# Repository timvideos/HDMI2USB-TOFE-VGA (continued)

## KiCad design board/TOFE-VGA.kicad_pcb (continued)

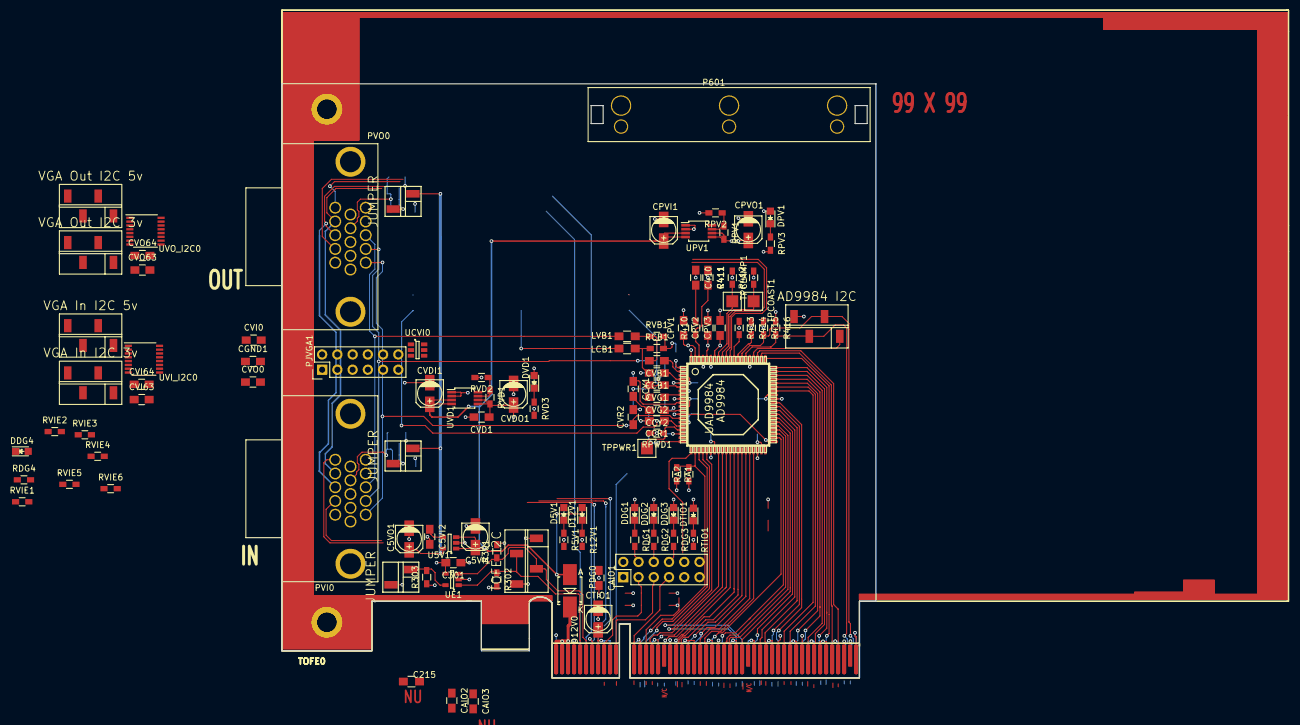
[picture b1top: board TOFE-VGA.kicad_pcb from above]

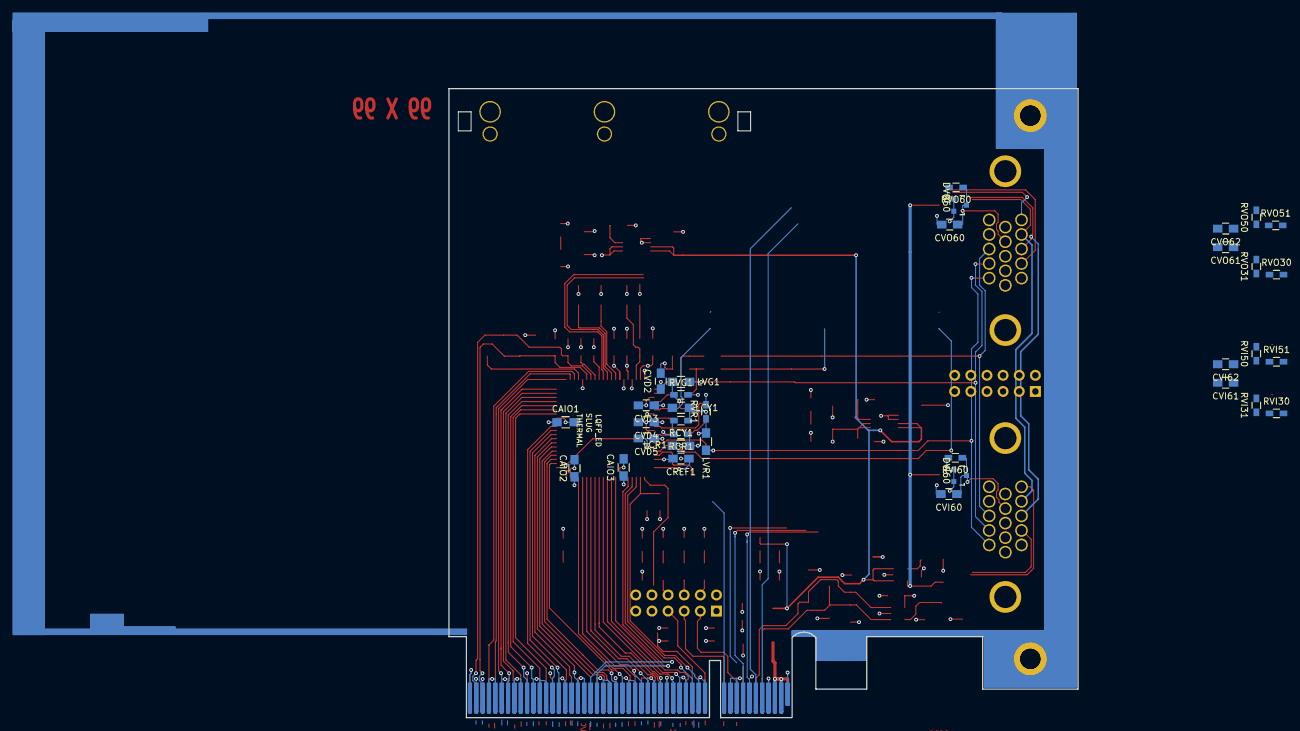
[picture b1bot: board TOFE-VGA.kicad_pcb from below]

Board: 4 copper layers, 141 parts (34 on the bottom side), 125 nets.

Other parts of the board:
C215: C5VI2; R_0805_HandSoldering
CAIO1#2, CAIO2#2, CAIO3#2: 100n; C_0805_HandSoldering
CGND1: 100n; C_0805_HandSoldering
TOFE0#2: TOFE-8X; TOFE_8X_HalfHeight

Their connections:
+3V3: CAIO1#2.1, CAIO2#2.1, CAIO3#2.1, TOFE0#2.A9, TOFE0#2.A10, TOFE0#2.B8, TOFE0#2.B10; also elsewhere on the board
/TOFE-VGA/AD9984/B0: TOFE0#2.B46; also elsewhere on the board
/TOFE-VGA/AD9984/B1: TOFE0#2.B45; also elsewhere on the board
/TOFE-VGA/AD9984/B2: TOFE0#2.A44; also elsewhere on the board
/TOFE-VGA/AD9984/B3: TOFE0#2.A43; also elsewhere on the board
/TOFE-VGA/AD9984/B4: TOFE0#2.B42; also elsewhere on the board
/TOFE-VGA/AD9984/B5: TOFE0#2.B41; also elsewhere on the board
/TOFE-VGA/AD9984/B6: TOFE0#2.A40; also elsewhere on the board
/TOFE-VGA/AD9984/B7: TOFE0#2.A39; also elsewhere on the board
/TOFE-VGA/AD9984/B8: TOFE0#2.B38; also elsewhere on the board
/TOFE-VGA/AD9984/B9: TOFE0#2.B37; also elsewhere on the board
/TOFE-VGA/AD9984/G0: TOFE0#2.A36; also elsewhere on the board
/TOFE-VGA/AD9984/G1: TOFE0#2.A35; also elsewhere on the board
/TOFE-VGA/AD9984/G2: TOFE0#2.B34; also elsewhere on the board
/TOFE-VGA/AD9984/G3: TOFE0#2.B33; also elsewhere on the board
/TOFE-VGA/AD9984/G4: TOFE0#2.A32; also elsewhere on the board
/TOFE-VGA/AD9984/G5: TOFE0#2.B30; also elsewhere on the board
/TOFE-VGA/AD9984/G6: TOFE0#2.B28; also elsewhere on the board
/TOFE-VGA/AD9984/G7: TOFE0#2.B27; also elsewhere on the board
/TOFE-VGA/AD9984/G8: TOFE0#2.A26; also elsewhere on the board
/TOFE-VGA/AD9984/G9: TOFE0#2.A25; also elsewhere on the board
/TOFE-VGA/AD9984/R0: TOFE0#2.B24; also elsewhere on the board
/TOFE-VGA/AD9984/R1: TOFE0#2.B23; also elsewhere on the board
/TOFE-VGA/AD9984/R2: TOFE0#2.A22; also elsewhere on the board
/TOFE-VGA/AD9984/R3: TOFE0#2.A21; also elsewhere on the board
/TOFE-VGA/AD9984/R4: TOFE0#2.B20; also elsewhere on the board
/TOFE-VGA/AD9984/R5: TOFE0#2.B19; also elsewhere on the board
/TOFE-VGA/AD9984/R6: TOFE0#2.A19; also elsewhere on the board
/TOFE-VGA/AD9984/R7: TOFE0#2.A17; also elsewhere on the board
/TOFE-VGA/AD9984/R8: TOFE0#2.A16; also elsewhere on the board
/TOFE-VGA/AD9984/R9: TOFE0#2.B15; also elsewhere on the board
/TOFE-VGA/TOFE/IDCLK: TOFE0#2.B5; also elsewhere on the board
/TOFE-VGA/TOFE/IDDAT: TOFE0#2.B6; also elsewhere on the board
/TOFE-VGA/TOFE/RAW_VCC12V: TOFE0#2.A2, TOFE0#2.A3, TOFE0#2.B1, TOFE0#2.B2, TOFE0#2.B3; also elsewhere on the board
GND: C215.2, CAIO1#2.2, CAIO2#2.2, CAIO3#2.2, CGND1.1, TOFE0#2.A4, TOFE0#2.A12, TOFE0#2.A15, TOFE0#2.A18, TOFE0#2.A20, TOFE0#2.A23, TOFE0#2.A24, TOFE0#2.A27, TOFE0#2.A28, TOFE0#2.A31, TOFE0#2.A34, TOFE0#2.A37, TOFE0#2.A38, TOFE0#2.A41, TOFE0#2.A42, TOFE0#2.A45, TOFE0#2.A46, TOFE0#2.A49, TOFE0#2.B4, TOFE0#2.B7, TOFE0#2.B13, TOFE0#2.B16, TOFE0#2.B18, TOFE0#2.B21, TOFE0#2.B22, TOFE0#2.B25, TOFE0#2.B26, TOFE0#2.B29, TOFE0#2.B32, TOFE0#2.B35, TOFE0#2.B36, TOFE0#2.B39, TOFE0#2.B40, TOFE0#2.B43, TOFE0#2.B44, TOFE0#2.B47, TOFE0#2.B49; also elsewhere on the board
GNDA: CGND1.2; also elsewhere on the board
unnamed 124: TOFE0#2.B12; also elsewhere on the board
unnamed 139: TOFE0#2.A33; also elsewhere on the board
unnamed 140: TOFE0#2.B17; also elsewhere on the board
unnamed 141: TOFE0#2.B31; also elsewhere on the board
PRNST: TOFE0#2.A1, TOFE0#2.B48; also elsewhere on the board

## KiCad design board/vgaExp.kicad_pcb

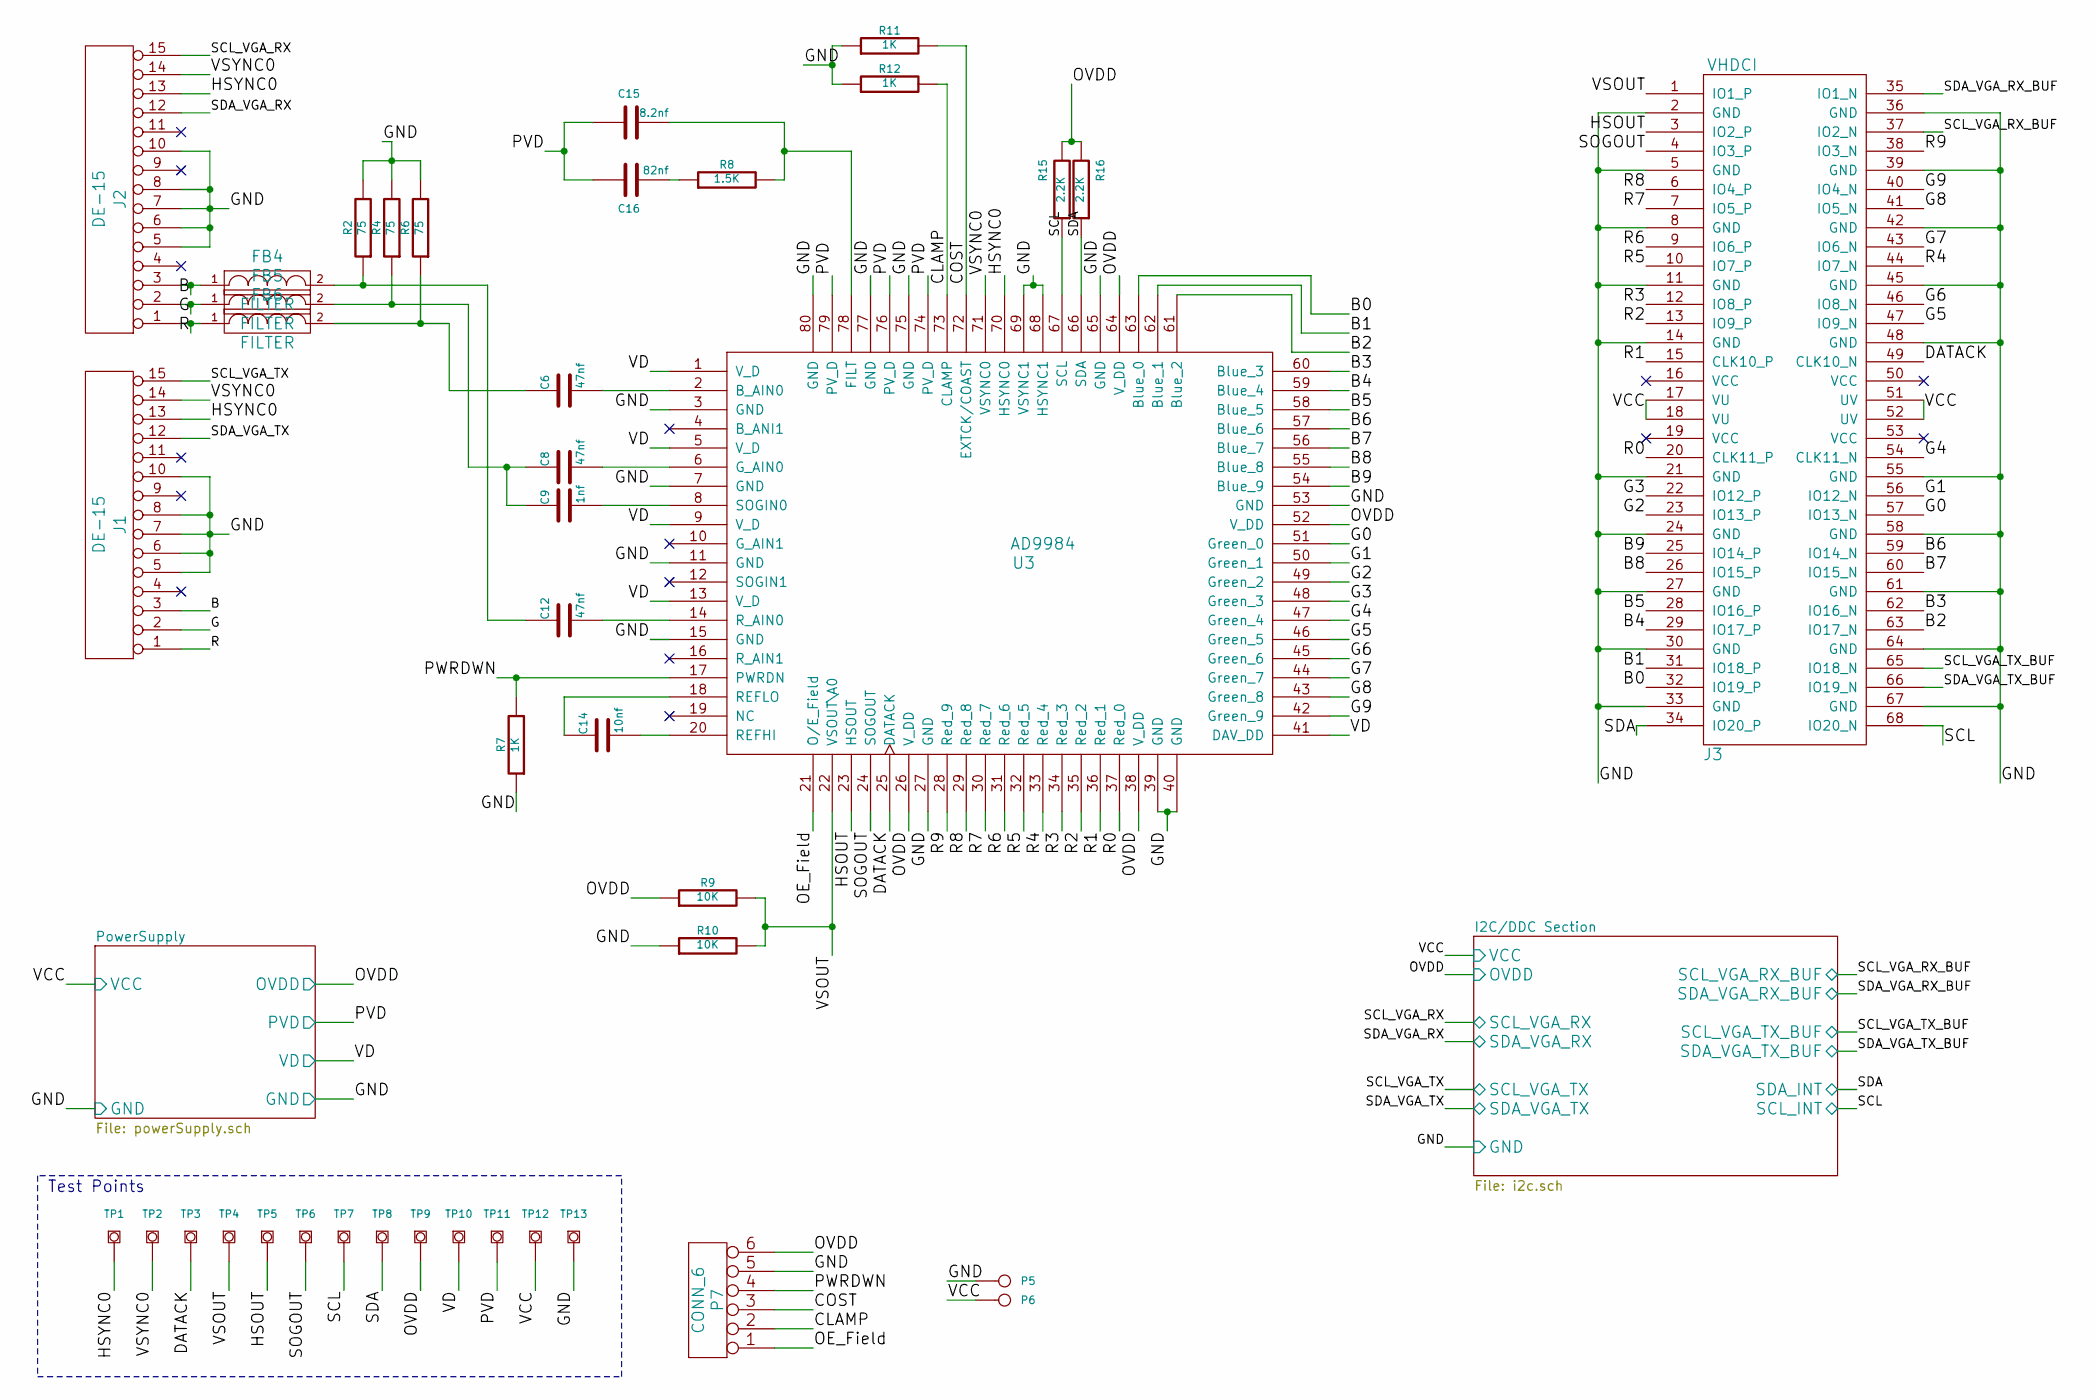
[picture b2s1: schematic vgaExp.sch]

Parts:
C6, C8, C12: 47nf
C9: 1nf
C14: 10nf
C15: 8.2nf
C16: 82nf
FB4, FB5, FB6: FILTER
J1, J2: DE-15
J3: VHDCI
P5, P6: CONN_1
P7: CONN_6
R2, R4, R6: 75
R7, R11, R12: 1K
R8: 1.5K
R9, R10: 10K
R15, R16: 2.2K
TP1, TP2, TP3, TP4, TP5, TP6, TP7, TP8, TP9, TP10, TP11, TP12, TP13: TESTPOINT
U3: AD9984

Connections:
/B: FB4.1, J1.3, J2.3
/B0: J3.32 (IO19_P), U3.63 (Blue_0)
/B1: J3.31 (IO18_P), U3.62 (Blue_1)
/B2: J3.63 (IO17_N), U3.61 (Blue_2)
/B3: J3.62 (IO16_N), U3.60 (Blue_3)
/B4: J3.29 (IO17_P), U3.59 (Blue_4)
/B5: J3.28 (IO16_P), U3.58 (Blue_5)
/B6: J3.59 (IO14_N), U3.57 (Blue_6)
/B7: J3.60 (IO15_N), U3.56 (Blue_7)
/B8: J3.26 (IO15_P), U3.55 (Blue_8)
/B9: J3.25 (IO14_P), U3.54 (Blue_9)
/CLAMP: P7.2, R12.2, U3.73 (CLAMP)
/COST: P7.3, R11.2, U3.72 (EXTCK/COAST)
/DATACK: J3.49 (CLK10_N), TP3.1, U3.25 (DATACK)
/G: FB5.1, J1.2, J2.2
/G0: J3.57 (IO13_N), U3.51 (Green_0)
/G1: J3.56 (IO12_N), U3.50 (Green_1)
/G2: J3.23 (IO13_P), U3.49 (Green_2)
/G3: J3.22 (IO12_P), U3.48 (Green_3)
/G4: J3.54 (CLK11_N), U3.47 (Green_4)
/G5: J3.47 (IO9_N), U3.46 (Green_5)
/G6: J3.46 (IO8_N), U3.45 (Green_6)
/G7: J3.43 (IO6_N), U3.44 (Green_7)
/G8: J3.41 (IO5_N), U3.43 (Green_8)
/G9: J3.40 (IO4_N), U3.42 (Green_9)
/HSOUT: J3.3 (IO2_P), TP5.1, U3.23 (HSOUT)
/HSYNC0: J1.13, J2.13, TP1.1, U3.70 (HSYNC0)
/I2C/DDC Section/SCL_INT: J3.68 (IO20_N), R15.1, TP7.1, U3.67 (SCL); also elsewhere on the board
/I2C/DDC Section/SCL_VGA_RX: J2.15; also elsewhere on the board
/I2C/DDC Section/SCL_VGA_RX_BUF: J3.37 (IO2_N); also elsewhere on the board
/I2C/DDC Section/SCL_VGA_TX: J1.15; also elsewhere on the board
/I2C/DDC Section/SCL_VGA_TX_BUF: J3.65 (IO18_N); also elsewhere on the board
/I2C/DDC Section/SDA_INT: J3.34 (IO20_P), R16.1, TP8.1, U3.66 (SDA); also elsewhere on the board
/I2C/DDC Section/SDA_VGA_RX: J2.12; also elsewhere on the board
/I2C/DDC Section/SDA_VGA_RX_BUF: J3.35 (IO1_N); also elsewhere on the board
/I2C/DDC Section/SDA_VGA_TX: J1.12; also elsewhere on the board
/I2C/DDC Section/SDA_VGA_TX_BUF: J3.66 (IO19_N); also elsewhere on the board
/I2C/DDC Section/VCC: J3.17 (VU), J3.18 (VU), J3.51 (UV), J3.52 (UV), P6.1, TP12.1; also elsewhere on the board
/OE_Field: P7.1, U3.21 (O/E_Field)
/PWRDWN: P7.4, R7.2, U3.17 (PWRDN)
/PowerSupply/PVD: C15.1, C16.1, TP11.1, U3.74 (PV_D), U3.76 (PV_D), U3.79 (PV_D); also elsewhere on the board
/PowerSupply/VD: TP10.1, U3.1 (V_D), U3.5 (V_D), U3.9 (V_D), U3.13 (V_D), U3.41 (DAV_DD); also elsewhere on the board
/R: FB6.1, J1.1, J2.1
/R0: J3.20 (CLK11_P), U3.37 (Red_0)
/R1: J3.15 (CLK10_P), U3.36 (Red_1)
/R2: J3.13 (IO9_P), U3.35 (Red_2)
/R3: J3.12 (IO8_P), U3.34 (Red_3)
/R4: J3.44 (IO7_N), U3.33 (Red_4)
/R5: J3.10 (IO7_P), U3.32 (Red_5)
/R6: J3.9 (IO6_P), U3.31 (Red_6)
/R7: J3.7 (IO5_P), U3.30 (Red_7)
/R8: J3.6 (IO4_P), U3.29 (Red_8)
/R9: J3.38 (IO3_N), U3.28 (Red_9)
/SOGOUT: J3.4 (IO3_P), TP6.1, U3.24 (SOGOUT)
/VSOUT: J3.1 (IO1_P), R9.2, R10.2, TP4.1, U3.22 (VSOUT\A0)
/VSYNC0: J1.14, J2.14, TP2.1, U3.71 (VSYNC0)
unnamed: C15.2, R8.2, U3.78 (FILT)
unnamed: C16.2, R8.1
unnamed: C6.2, U3.2 (B_AIN0)
unnamed: C8.2, U3.6 (G_AIN0)
unnamed: C9.2, U3.8 (SOGIN0)
unnamed: C12.2, U3.14 (R_AIN0)
unnamed: C12.1, FB4.2, R2.1
unnamed: C8.1, C9.1, FB5.2, R4.1
unnamed: C6.1, FB6.2, R6.1
unnamed: C14.2, U3.20 (REFHI)
unnamed: C14.1, U3.18 (REFLO)

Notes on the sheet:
Test Points

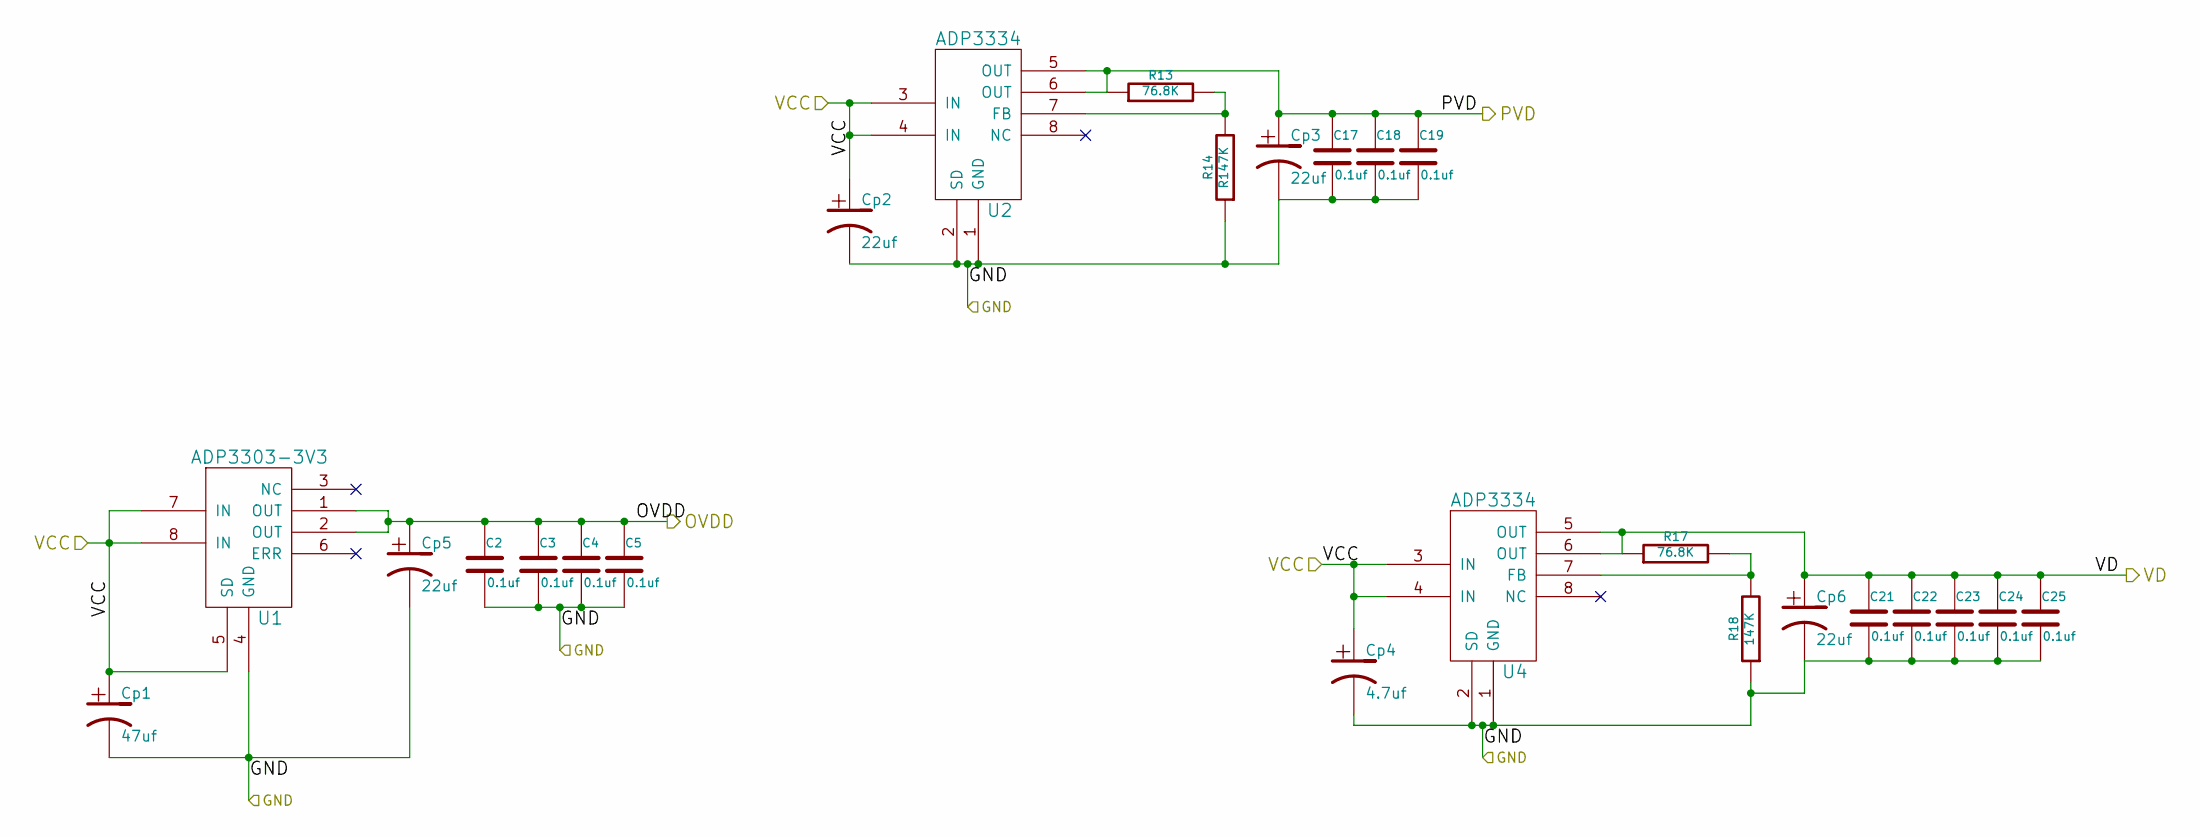
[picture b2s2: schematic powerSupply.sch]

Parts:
C2, C3, C4, C5, C17, C18, C19, C21, C22, C23, C24, C25: 0.1uf
Cp1: 47uf
Cp2, Cp3, Cp5, Cp6: 22uf
Cp4: 4.7uf
R13, R17: 76.8K
R14: R147K
R18: 147K
U1: ADP3303-3V3
U2, U4: ADP3334

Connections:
/I2C/DDC Section/VCC: Cp1.1, Cp2.1, Cp4.1, U1.5 (SD), U1.7 (IN), U1.8 (IN), U2.3 (IN), U2.4 (IN), U4.3 (IN), U4.4 (IN); also elsewhere on the board
/PowerSupply/PVD: C17.1, C18.1, C19.1, Cp3.1, R13.1, U2.5 (OUT), U2.6 (OUT); also elsewhere on the board
/PowerSupply/VD: C21.1, C22.1, C23.1, C24.1, C25.1, Cp6.1, R17.1, U4.5 (OUT), U4.6 (OUT); also elsewhere on the board
unnamed: R13.2, R14.2, U2.7 (FB)
unnamed: R17.2, R18.2, U4.7 (FB)

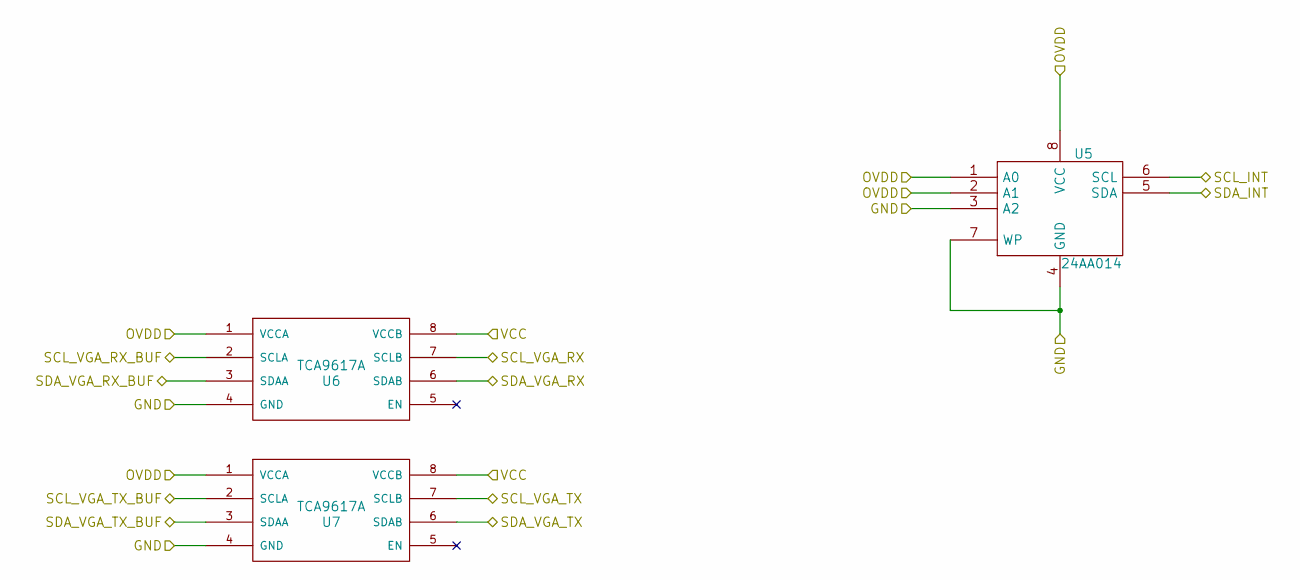
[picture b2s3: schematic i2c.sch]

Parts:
U5: 24AA014
U6, U7: TCA9617A

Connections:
/I2C/DDC Section/SCL_INT: U5.6 (SCL); also elsewhere on the board
/I2C/DDC Section/SCL_VGA_RX: U6.7 (SCLB); also elsewhere on the board
/I2C/DDC Section/SCL_VGA_RX_BUF: U6.2 (SCLA); also elsewhere on the board
/I2C/DDC Section/SCL_VGA_TX: U7.7 (SCLB); also elsewhere on the board
/I2C/DDC Section/SCL_VGA_TX_BUF: U7.2 (SCLA); also elsewhere on the board
/I2C/DDC Section/SDA_INT: U5.5 (SDA); also elsewhere on the board
/I2C/DDC Section/SDA_VGA_RX: U6.6 (SDAB); also elsewhere on the board
/I2C/DDC Section/SDA_VGA_RX_BUF: U6.3 (SDAA); also elsewhere on the board
/I2C/DDC Section/SDA_VGA_TX: U7.6 (SDAB); also elsewhere on the board
/I2C/DDC Section/SDA_VGA_TX_BUF: U7.3 (SDAA); also elsewhere on the board
/I2C/DDC Section/VCC: U6.8 (VCCB), U7.8 (VCCB); also elsewhere on the board

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
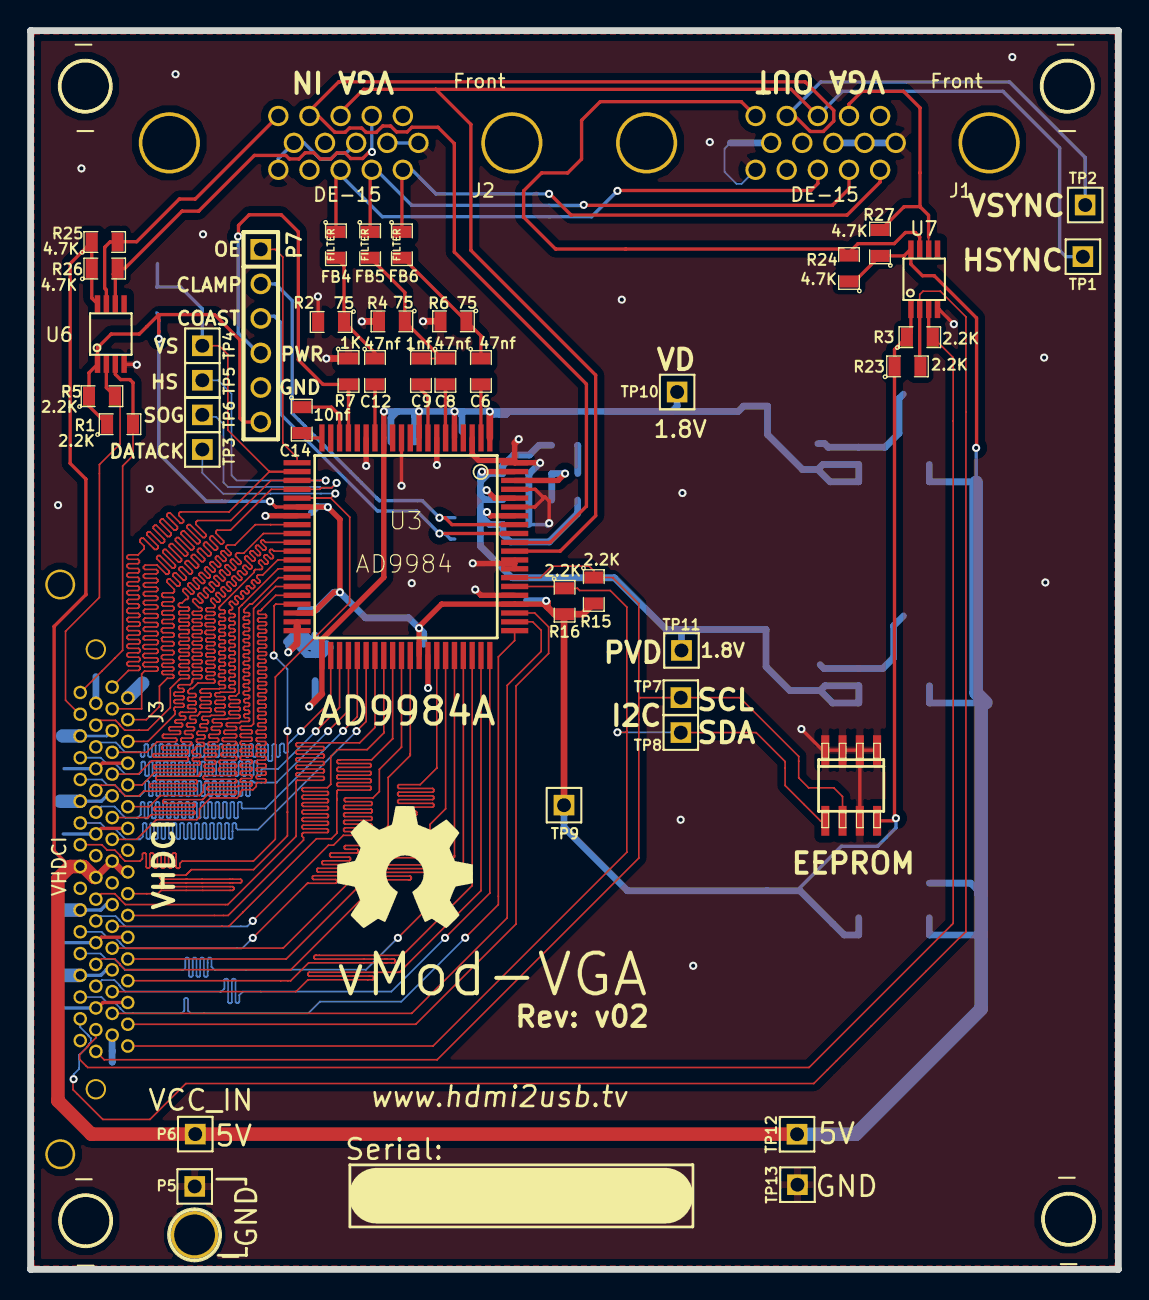
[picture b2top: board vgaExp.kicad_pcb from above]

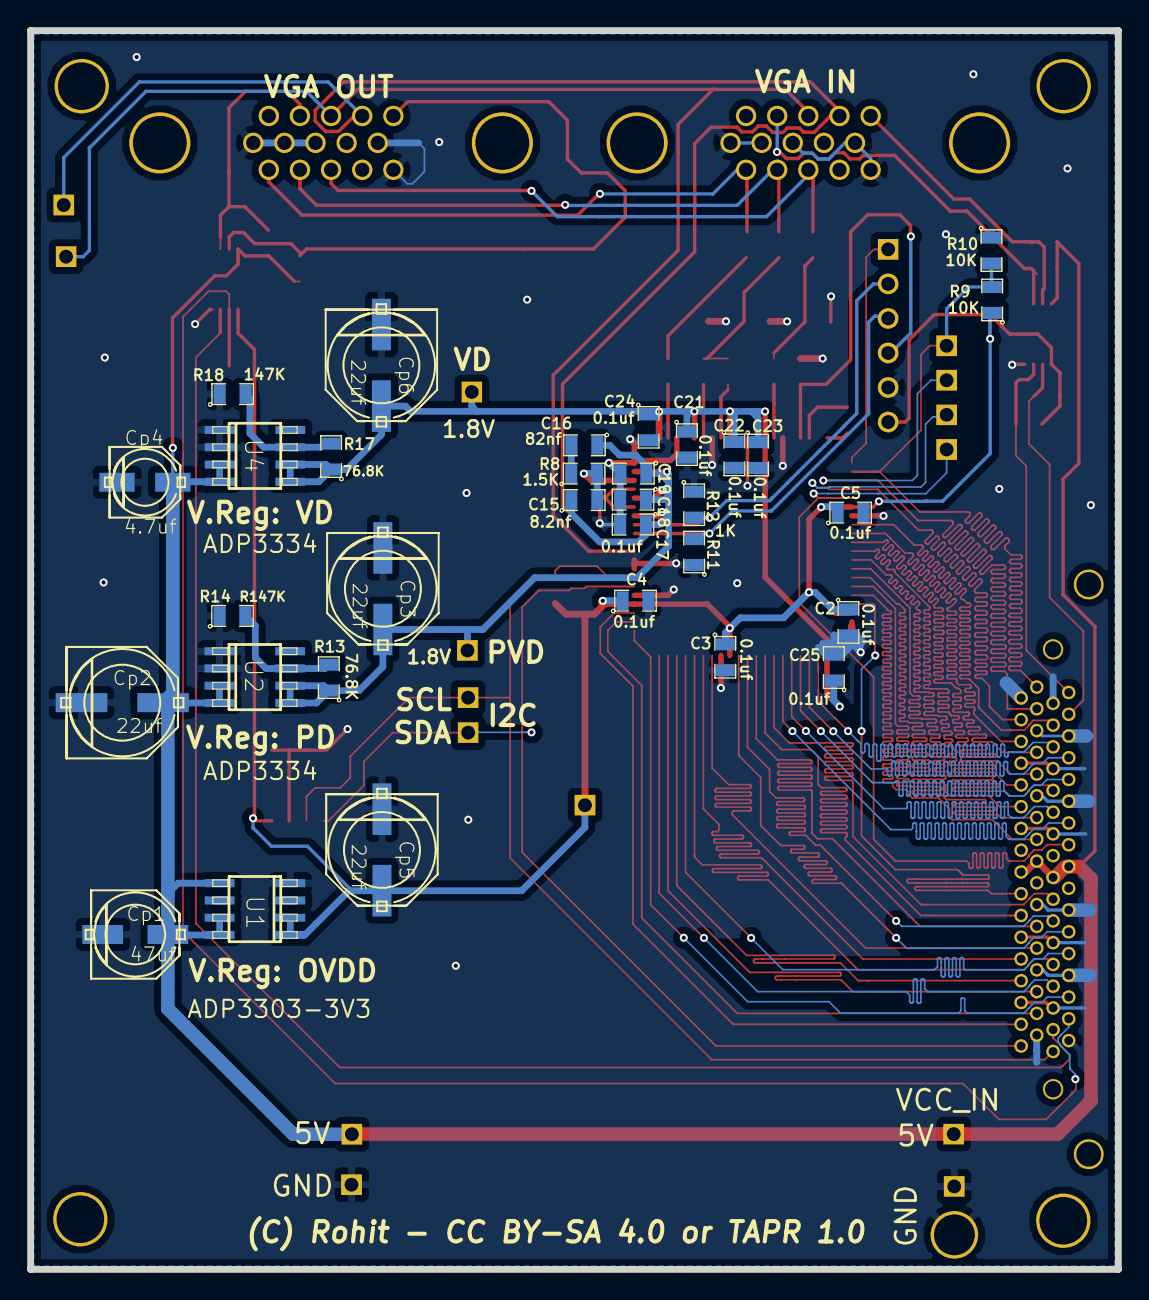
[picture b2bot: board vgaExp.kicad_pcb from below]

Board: 2 copper layers, 80.0 x 91.1 mm, 83 parts (32 on the bottom side), 71 nets.

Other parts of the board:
-: -; STAND-OFF
-#2, -#3, -#4: -; STAND-OFF
-#5: GND-HOLE
R1, R3, R5, R23: 2.2K; SM0805
R24, R25, R26, R27: 4.7K; SM0805
l1: e; OSHW-logo_silkscreen-back_10mm

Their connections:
/I2C/DDC Section/SCL_VGA_RX: R25.2; also elsewhere on the board
/I2C/DDC Section/SCL_VGA_RX_BUF: R5.2; also elsewhere on the board
/I2C/DDC Section/SCL_VGA_TX: R24.2; also elsewhere on the board
/I2C/DDC Section/SCL_VGA_TX_BUF: R23.2; also elsewhere on the board
/I2C/DDC Section/SDA_VGA_RX: R26.2; also elsewhere on the board
/I2C/DDC Section/SDA_VGA_RX_BUF: R1.2; also elsewhere on the board
/I2C/DDC Section/SDA_VGA_TX: R27.2; also elsewhere on the board
/I2C/DDC Section/SDA_VGA_TX_BUF: R3.2; also elsewhere on the board
/I2C/DDC Section/VCC: R24.1, R25.1, R26.1, R27.1; also elsewhere on the board

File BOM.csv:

1nf,2,"C9 C11"
8.2nf,1,"C15"
47nf,6,"C6 C7 C8 C10 C12 C13"
82nf,1,"C16"
10uf,1,"C14"
.1uf,12,"C2 C3 C4 C5 C17 C18 C19 C21 C22 C23 C24 C25"
4.7uf,1,"Cp4"
22uf,4,"Cp2 Cp3 Cp5 Cp6"
47uf,1,"Cp1"
FILTER,6,"FB1 FB2 FB3 FB4 FB5 FB6"
DE-15,2,"J1 J2"
VHDCI,1,"J3"
75,6,"R1 R2 R3 R4 R5 R6"
1K,3,"R7 R11 R12"
1.5K,1,"R8"
2.2K,2,"R15 R16"
10K,2,"R9 R10"
76.8k,2,"R13 R17"
147k,2,"R14 R18"
ADP3303-3V3,1,"U1"
ADP3334,2,"U2 U4"
AD9984,1,"U3"

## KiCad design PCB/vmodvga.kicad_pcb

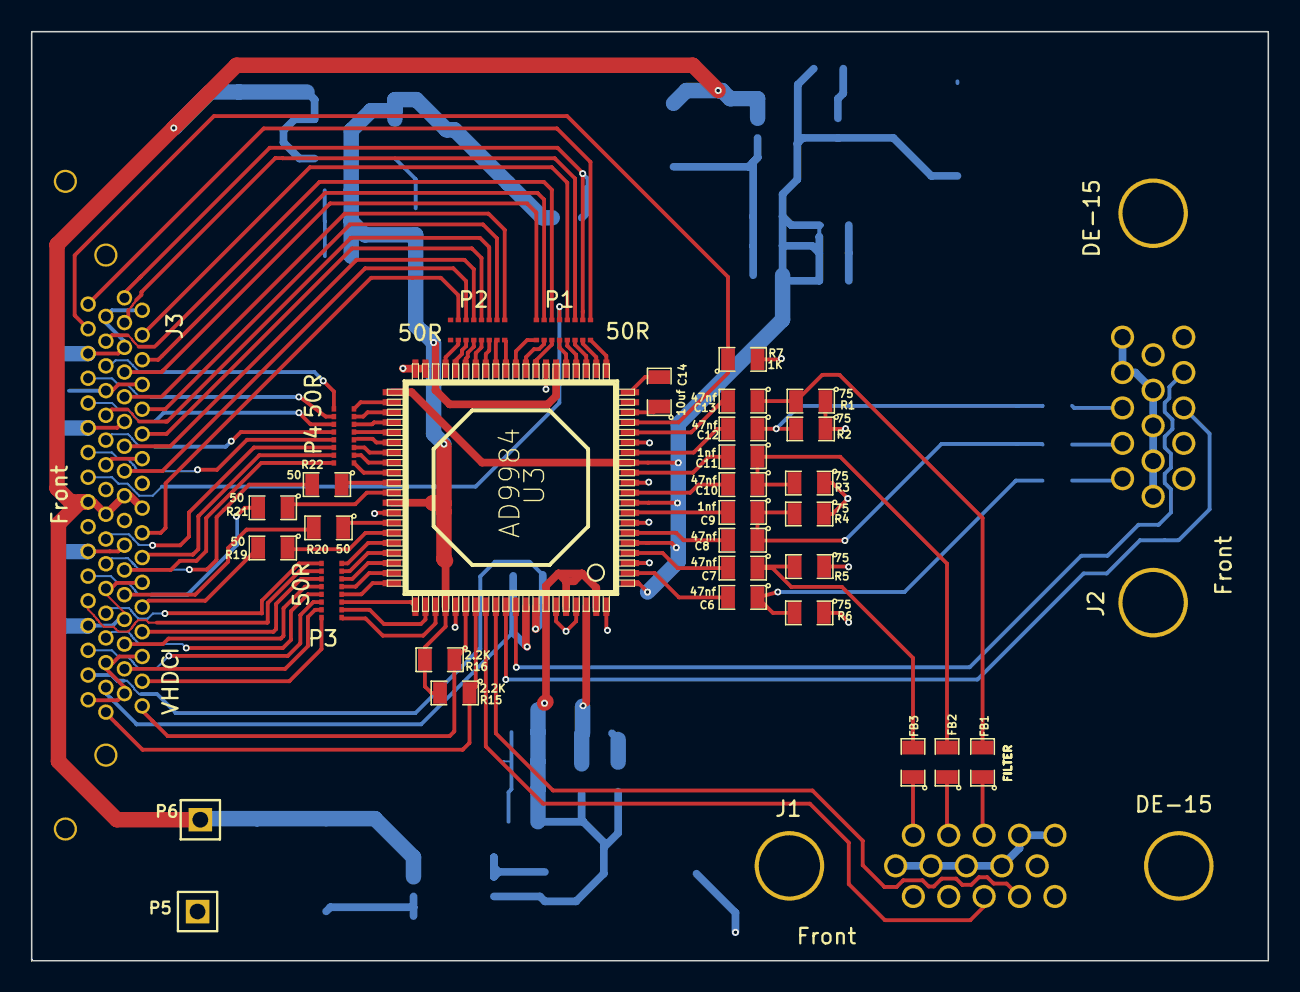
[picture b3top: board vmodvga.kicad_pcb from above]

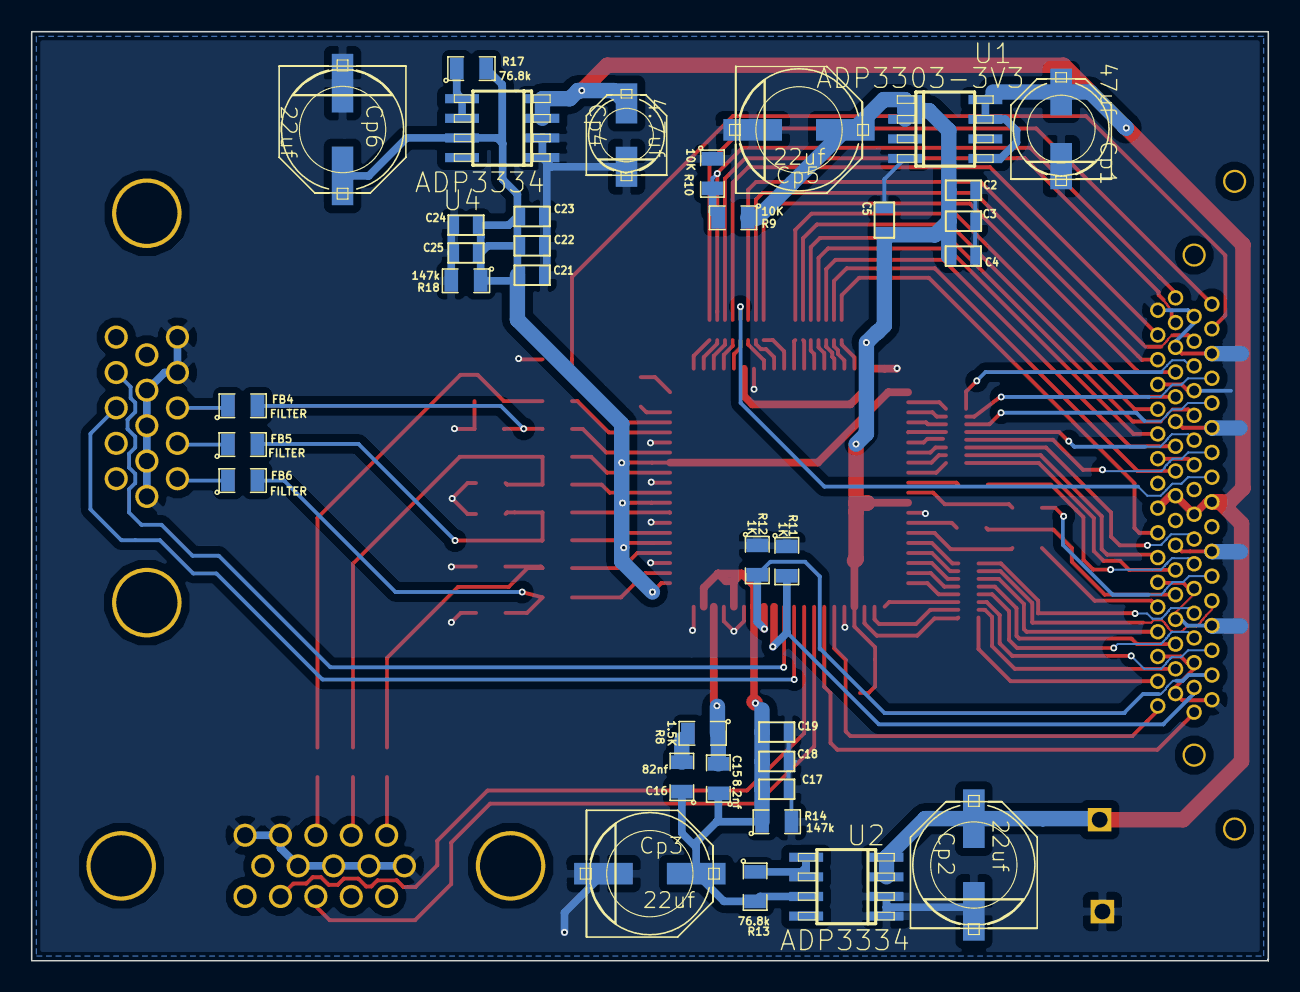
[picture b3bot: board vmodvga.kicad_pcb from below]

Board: 2 copper layers, 80.0 x 60.1 mm, 70 parts (35 on the bottom side), 110 nets.

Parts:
C2, C3, C4, C5, C17, C18, C19, C21, C22, C23, C24, C25: .1uf; SM0603
C6, C7, C8, C10, C12, C13: 47nf; SM0805
C9, C11: 1nf; SM0805
C14: 10uf; SM0805
C15: 8.2nf; SM0805
C16: 82nf; SM0805
Cp1: 47uf; -PANASONIC_D
Cp2, Cp3, Cp5, Cp6: 22uf; -PANASONIC_E
Cp4: 4.7uf; -PANASONIC_C
FB1, FB2, FB3, FB4, FB5, FB6: FILTER; SM0805
J1, J2: DE-15
J3: VHDCI
P1, P2, P3, P4: 50R; R50x8
P5, P6: CONN_1; PIN_ARRAY_1
R1, R2, R3, R4, R5, R6: 75; SM0805
R7, R11, R12: 1K; SM0805
R8: 1.5K; SM0805
R9, R10: 10K; SM0805
R13, R17: 76.8k; SM0805
R14, R18: 147k; SM0805
R15, R16: 2.2K; SM0805
R19, R20, R21, R22: 50; SM0805
U1: ADP3303-3V3; -SOIC8
U2, U4: ADP3334; -SOIC8
U3: AD9984; analog-devices2-LQFP80

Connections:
/B0: J3.32, P3.8
/B1: J3.31, P3.7
/B2: J3.63, P3.6
/B3: J3.62, P3.5
/B4: J3.29, P3.4
/B5: J3.28, P3.3
/B6: J3.59, P3.2
/B7: J3.60, P3.1
/B8: J3.26, R19.2
/B9: J3.25, R20.2
/CLAMP: J3.65, R12.2, U3.73
/COST: J3.66, R11.2, U3.72
/DATACK: J3.49, P1.13
/G0: J3.57, R21.2
/G1: J3.56, R22.2
/G2: J3.23, P4.16
/G3: J3.22, P4.15
/G4: J3.54, P4.14
/G5: J3.47, P4.13
/G6: J3.46, P4.12
/G7: J3.43, P4.11
/G8: J3.41, P4.10
/G9: J3.40, P4.9
/GND: C2.2, C3.2, C4.2, C5.2, C17.2, C18.2, C19.2, C21.2, C22.2, C23.2, C24.2, C25.2, Cp1.-, Cp2.-, Cp3.-, Cp4.-, Cp5.-, Cp6.-, J1.4, J1.5, J1.6, J1.7, J1.8, J1.9, J2.4, J2.5, J2.6, J2.7, J2.8, J2.9, J3.2, J3.5, J3.8, J3.11, J3.14, J3.21, J3.24, J3.27, J3.30, J3.33, J3.36, J3.39, J3.42, J3.45, J3.48, J3.55, J3.58, J3.61, J3.64, J3.67, P5.1, R1.1, R2.1, R3.1, R4.1, R5.1, R6.1, R7.2, R10.1, R11.1, R12.1, R14.2, R18.2, U1.4, U2.1, U2.2, U3.3, U3.7, U3.11, U3.15, U3.27, U3.39, U3.40, U3.53, U3.65, U3.75, U3.77, U3.80, U4.1, U4.2
/HSOUT: J3.3, P1.11
/HSYNC0: J2.13, U3.70
/HSYNC1: J1.13, U3.68
/OE_Field: J3.35, P1.9
/OVDD: C2.1, C3.1, C4.1, C5.1, Cp5.+, R9.1, R15.2, R16.2, U1.1, U1.2, U3.26, U3.38, U3.52, U3.64
/PVD: C15.1, C16.1, C17.1, C18.1, C19.1, Cp3.+, R13.2, R14.1, U2.7, U3.74, U3.76, U3.79
/PWRDWN: J3.37, R7.1, U3.17
/R0: J3.20, P2.15
/R1: J3.15, P2.14
/R2: J3.13, P2.13
/R3: J3.12, P2.12
/R4: J3.44, P2.11
/R5: J3.10, P2.10
/R6: J3.9, P2.9
/R7: J3.7, P1.16
/R8: J3.6, P1.15
/R9: J3.38, P1.14
/SCL: J3.68, R15.1, U3.67
/SDA: J3.34, R16.1, U3.66
/SOGOUT: J3.4, P1.12
/VCC: Cp1.+, Cp2.+, Cp4.+, J3.17, J3.18, J3.51, J3.52, P6.1, U1.5, U1.7, U1.8, U2.3, U2.4, U4.3, U4.4
/VD: C21.1, C22.1, C23.1, C24.1, C25.1, Cp6.+, R17.2, R18.1, U3.1, U3.5, U3.9, U3.13, U3.41, U4.7
/VSOUT: J3.1, P1.10, R9.2, R10.2
/VSYNC0: J2.14, U3.71
/VSYNC1: J1.14, U3.69
unnamed: R13.1, U2.5, U2.6
unnamed: R17.1, U4.5, U4.6
unnamed: C12.2, U3.14
unnamed: C8.2, U3.6
unnamed: C6.2, U3.2
unnamed: C9.2, U3.8
unnamed: C14.2, U3.20
unnamed: C14.1, U3.18
unnamed: R22.1, U3.50
unnamed: P3.12, U3.60
unnamed: P3.13, U3.59
unnamed: P3.14, U3.58
unnamed: P3.15, U3.57
unnamed: P3.16, U3.56
unnamed: R19.1, U3.55
unnamed: R20.1, U3.54
unnamed: R21.1, U3.51
unnamed: P4.1, U3.49
unnamed: P4.2, U3.48
unnamed: P4.3, U3.47
unnamed: P4.4, U3.46
unnamed: P4.5, U3.45
unnamed: P4.6, U3.44
unnamed: P4.7, U3.43
unnamed: P4.8, U3.42
unnamed: P3.10, U3.62
unnamed: P1.2, U3.29
unnamed: P1.1, U3.30
unnamed: P2.8, U3.31
unnamed: P2.7, U3.32
unnamed: P2.6, U3.33
unnamed: P2.5, U3.34
unnamed: P2.4, U3.35
unnamed: P2.3, U3.36
unnamed: P2.2, U3.37
unnamed: P3.11, U3.61
unnamed: P1.3, U3.28
unnamed: P3.9, U3.63
unnamed: FB4.1, J2.3
unnamed: FB6.1, J2.1
unnamed: P1.8, U3.21
unnamed: P1.7, U3.22
unnamed: P1.6, U3.23
unnamed: P1.5, U3.24
unnamed: P1.4, U3.25
unnamed: C7.1, FB3.2, R5.2
unnamed: C13.1, FB1.2, R1.2
unnamed: C8.1, C9.1, FB5.2, R4.2
unnamed: C6.1, FB6.2, R6.2
unnamed: FB1.1, J1.3
unnamed: FB2.1, J1.2
unnamed: FB3.1, J1.1
unnamed: FB5.1, J2.2
unnamed: C12.1, FB4.2, R2.2
unnamed: C16.2, R8.2
unnamed: C10.1, C11.1, FB2.2, R3.2
unnamed: C10.2, U3.10
unnamed: C11.2, U3.12
unnamed: C13.2, U3.16
unnamed: C7.2, U3.4
unnamed: C15.2, R8.1, U3.78

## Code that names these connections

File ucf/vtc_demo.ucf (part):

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
 # onboard VHDCI
# Channnel 1 connects to P signals, Channel 2 to N signals
 NET "VSOUT"  LOC = "U16" |IOSTANDARD = LVCMOS33 ; # Bank = 2,  Pin name = IO_L2P_CMPCLK,       Sch name = EXP-IO1_P
 NET "HSOUT"  LOC = "U15" |IOSTANDARD = LVCMOS33 ; # Bank = 2,  Pin name = *IO_L5P,        		Sch name = EXP-IO2_P
 NET "SOGOUT"  LOC = "U13" |IOSTANDARD = LVCMOS33 ; # Bank = 2,  Pin name = IO_L14P_D11,        Sch name = EXP-IO3_P
 NET "R<8>"  LOC = "M11" |IOSTANDARD = LVCMOS33 ; # Bank = 2,  Pin name = *IO_L15P,        		Sch name = EXP-IO4_P
 NET "R<7>"  LOC = "R11" |IOSTANDARD = LVCMOS33 ; # Bank = 2,  Pin name = IO_L16P,        		Sch name = EXP-IO5_P
 NET "R<6>"  LOC = "T12" |IOSTANDARD = LVCMOS33 ; # Bank = 2,  Pin name = *IO_L19P,        		Sch name = EXP-IO6_P
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 NET "B<0>" LOC = "N6" |IOSTANDARD = LVCMOS33 ;  # Bank = 2,  Pin name = *IO_L47P,        		Sch name = EXP-IO19_P
 #NET "SDA" LOC = "U5"| IOSTANDARD = LVCMOS33 ;  # Bank = 2,  Pin name = IO_49P_D3,        		Sch name = EXP-IO20_P

 #NET "OE_FIELD"  LOC = "V16"; # Bank = 2,  Pin name = IO_L2N_CMPMOSI,  Sch name = EXP-IO1_N
 #NET "PWRDWN"  LOC = "V15"; # Bank = 2,  Pin name = *IO_L5N,        	Sch name = EXP-IO2_N
 NET "R<9>"  LOC = "V13" |IOSTANDARD = LVCMOS33 ; # Bank = 2,  Pin name = IO_L14N_D12,        	Sch name = EXP-IO3_N
 NET "G<9>"  LOC = "N11" |IOSTANDARD = LVCMOS33 ; # Bank = 2,  Pin name = *IO_L15N,        		Sch name = EXP-IO4_N
 NET "G<8>"  LOC = "T11" |IOSTANDARD = LVCMOS33 ; # Bank = 2,  Pin name = IO_L16N_VREF,        	Sch name = EXP-IO5_N
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 NET "R<4>"  LOC = "P11" |IOSTANDARD = LVCMOS33 ; # Bank = 2,  Pin name = *IO_L20N,        		Sch name = EXP-IO7_N
 NET "G<6>"  LOC = "N9" |IOSTANDARD = LVCMOS33 ;  # Bank = 2,  Pin name = *IO_L22N,        		Sch name = EXP-IO8_N
 NET "G<5>"  LOC = "V11" |IOSTANDARD = LVCMOS33 ; # Bank = 2,  Pin name = IO_L23N,        		Sch name = EXP-IO9_N
 NET "DATACK"  LOC = "T10" |IOSTANDARD = LVCMOS33 ; # Bank = 2,  Pin name = IO_L29N_GCLK2,      Sch name = EXP-IO10_N
 NET "G<4>" LOC = "V10" |IOSTANDARD = LVCMOS33 ; # Bank = 2,  Pin name = IO_L30N_GCLK0_USERCCLK,Sch name = EXP-IO11_N
 NET "G<1>" LOC = "T8" |IOSTANDARD = LVCMOS33 ;  # Bank = 2,  Pin name = IO_L31N_GCLK30_D15,    Sch name = EXP-IO12_N
 NET "G<0>" LOC = "N8" |IOSTANDARD = LVCMOS33 ;  # Bank = 2,  Pin name = *IO_L40N,        		Sch name = EXP-IO13_N
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 NET "B<7>" LOC = "V7" |IOSTANDARD = LVCMOS33 ;  # Bank = 2,  Pin name = IO_L43N,        			Sch name = EXP-IO15_N
 NET "B<3>" LOC = "P8" |IOSTANDARD = LVCMOS33 ;  # Bank = 2,  Pin name = *IO_L44N,        		Sch name = EXP-IO16_N
 NET "B<2>" LOC = "V6" |IOSTANDARD = LVCMOS33 ;  # Bank = 2,  Pin name = IO_L45N,        			Sch name = EXP-IO17_N
 #NET "CLAMP" LOC = "T7";  # Bank = 2,  Pin name = IO_L46N,        		Sch name = EXP-IO18_N
 #NET "COAST" LOC = "P7";  # Bank = 2,  Pin name = *IO_L47N,        		Sch name = EXP-IO19_N
 #NET "SCL" LOC = "V5"| IOSTANDARD = LVCMOS33 ;  # Bank = 2,  Pin name = IO_49N_D4,        		Sch name = EXP-IO20_N 


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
